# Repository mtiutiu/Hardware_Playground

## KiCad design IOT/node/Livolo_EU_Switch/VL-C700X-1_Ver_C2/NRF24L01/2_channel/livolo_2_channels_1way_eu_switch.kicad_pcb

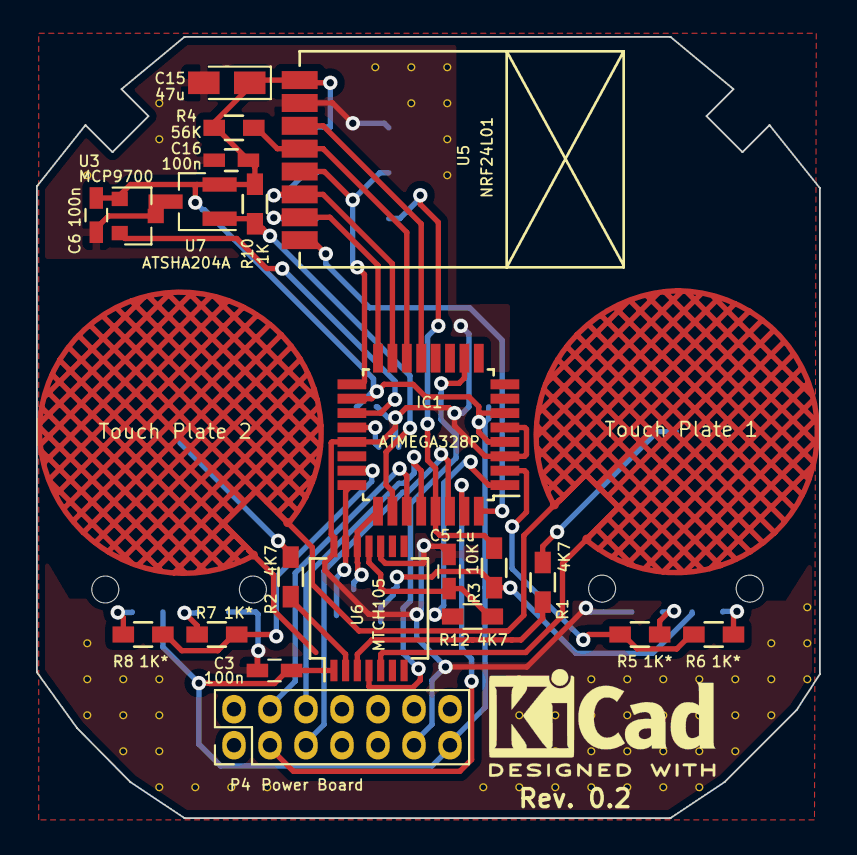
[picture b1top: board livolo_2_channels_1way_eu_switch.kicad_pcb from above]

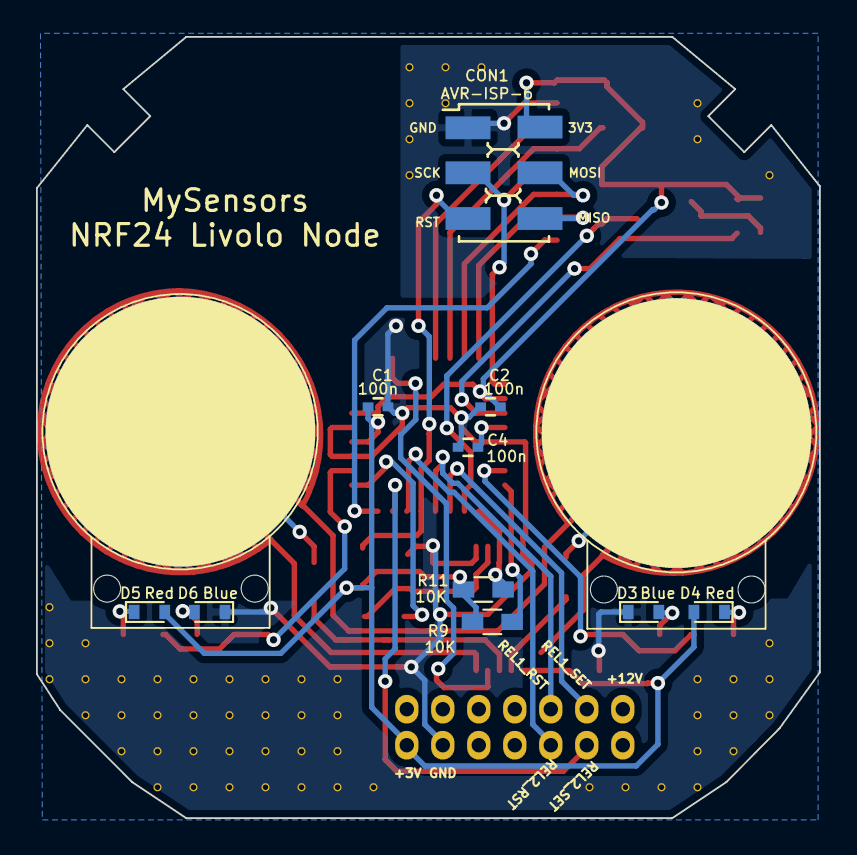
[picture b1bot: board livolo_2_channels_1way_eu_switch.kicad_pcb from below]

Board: 2 copper layers, 43.5 x 43.4 mm, 90 parts (10 on the bottom side), 32 nets.

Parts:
C1, C2, C4: 100n; C_0402
C3, C6, C16: 100n; C_0603_HandSoldering
C5: 1u; C_0603_HandSoldering
C15: 47u; CP_Tantalum_Case-R_EIA-2012-12_Wave
CON1: AVR-ISP-6; AVR_ISP_SMT_Small_02x03
D3, D6: Blue; D_0603
D4, D5: Red; D_0603
IC1: ATMEGA328P; TQFP-32_7x7mm_Pitch0.8mm
P4: Power Board; Pin_Header_Straight_2x07_Pitch2.00mm
R1, R2, R12: 4K7; R_0603_HandSoldering
R3, R9, R11: 10K; R_0603_HandSoldering
R4: 56K; R_0603_HandSoldering
R5, R6, R7, R8: 1K*; R_0603_HandSoldering
R10: 1K; R_0603_HandSoldering
U1: Touch Plate 2; livolo_ts_guard_cut_simple
U2: Touch Plate 1; livolo_ts_guard_cut_simple
U3: MCP9700; SOT-23
U5: NRF24L01; NRF24L01-SMD
U6: MTCH105; SSOP-14_5.3x6.2mm_Pitch0.65mm
U7: ATSHA204A; SOT-23_Handsoldering
V2_4, V2_17, V2_18, V2_19, V3_18, V3_19, V3_20, V4_2, V4_3, V4_18, V4_19, V4_20, V4_21, V5_21, V6_21, V7_21, V10_1, V11_1, V11_2, V12_1, V12_2, V12_3, V12_4, V13_21, V14_18, V14_19, V14_20, V14_21, V15_18, V15_19, V15_20, V15_21, V16_18, V16_19, V16_20, V16_21, V17_18, V17_19, V17_20, V17_21, V18_18, V18_19, V18_20, V18_21, V19_18, V19_19, V19_20, V19_21, V20_18, V20_19, V20_20, V21_17, V21_18, V21_19, V22_16, V22_17, V22_18: AUTO_VIA; VIA_MATRIX

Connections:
+3V3: C1.1, C2.2, C3.1, C6.2, C15.1, C16.2, CON1.2, D4.2, D5.2, IC1.4, IC1.6, IC1.18, P4.13, R3.1, R4.2, R9.1, R10.1, R11.1, U3.1, U5.2, U6.1, U7.2
/ATSHA204A: IC1.26, R10.2, U7.1
/MISO: CON1.6, IC1.16, U5.7
/MOSI: CON1.4, IC1.15, U5.6
/MTPM: IC1.10, U6.4
/MTSA: IC1.1, R12.1
/RADIO_CE: IC1.13, U5.3
/RADIO_CSN: IC1.14, R4.1, U5.4
/RADIO_IRQ: IC1.32, U5.8
/RESET: CON1.5, IC1.29, R3.2
/Relay1_Reset: IC1.28, P4.6
/Relay1_Set: IC1.27, P4.4
/Relay2_Reset: IC1.31, P4.3
/Relay2_Set: IC1.30, P4.5
/S1_LEDs: IC1.2, R5.2, R6.2
/S2_LEDs: IC1.23, R7.2, R8.2
/SCK: CON1.3, IC1.17, U5.5
/TEMP_SENS: IC1.19, U3.2
/TS1: IC1.24, R9.2, U6.13
/TS2: IC1.25, R11.2, U6.12
GND: C1.2, C2.1, C3.2, C4.1, C5.2, C6.1, C15.2, C16.1, CON1.1, D3.1, D6.1, IC1.3, IC1.5, IC1.21, P4.11, U3.3, U5.1, U6.10, U6.14, U7.3, V2_4.1, V2_17.1, V2_18.1, V2_19.1, V3_18.1, V3_19.1, V3_20.1, V4_2.1, V4_3.1, V4_18.1, V4_19.1, V4_20.1, V4_21.1, V5_21.1, V6_21.1, V7_21.1, V10_1.1, V11_1.1, V11_2.1, V12_1.1, V12_2.1, V12_3.1, V12_4.1, V13_21.1, V14_18.1, V14_19.1, V14_20.1, V14_21.1, V15_18.1, V15_19.1, V15_20.1, V15_21.1, V16_18.1, V16_19.1, V16_20.1, V16_21.1, V17_18.1, V17_19.1, V17_20.1, V17_21.1, V18_18.1, V18_19.1, V18_20.1, V18_21.1, V19_18.1, V19_19.1, V19_20.1, V19_21.1, V20_18.1, V20_19.1, V20_20.1, V21_17.1, V21_18.1, V21_19.1, V22_16.1, V22_17.1, V22_18.1
unnamed: C4.2, IC1.20
unnamed: C5.1, R12.2, U6.11
unnamed: D3.2, R7.1
unnamed: D4.1, R8.1
unnamed: D5.1, R6.1
unnamed: D6.2, R5.1
unnamed: R1.1, U6.3
unnamed: R1.2, U2.1
unnamed: R2.1, U1.1
unnamed: R2.2, U6.2
unnamed: U1.2, U2.2, U6.5

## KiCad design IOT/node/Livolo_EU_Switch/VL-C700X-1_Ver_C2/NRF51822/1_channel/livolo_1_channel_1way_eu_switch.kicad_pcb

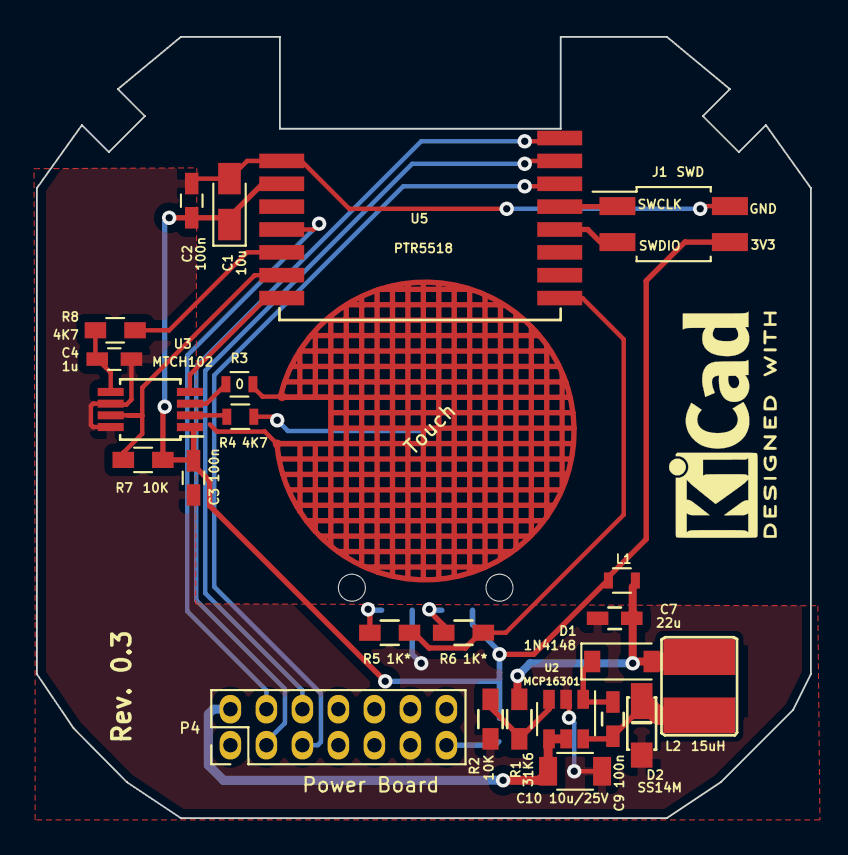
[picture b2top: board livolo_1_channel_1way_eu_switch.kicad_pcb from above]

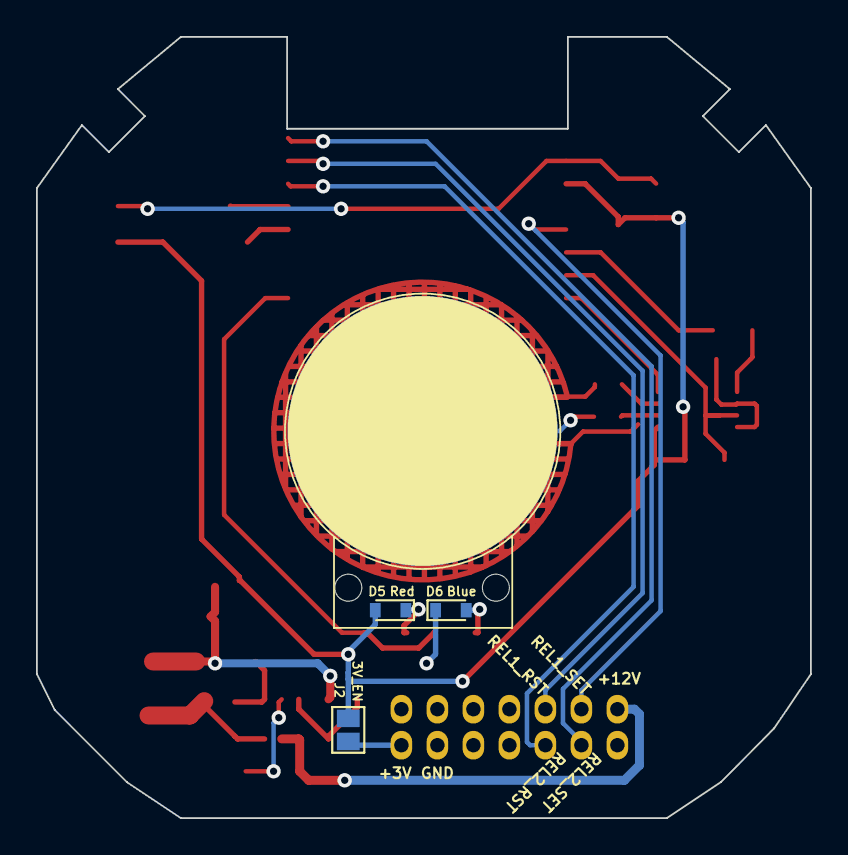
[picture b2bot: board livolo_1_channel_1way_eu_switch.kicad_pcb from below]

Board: 2 copper layers, 43.0 x 43.4 mm, 28 parts (3 on the bottom side), 25 nets.

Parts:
C1: 10u; CP_Tantalum_Case-R_EIA-2012-12_Wave
C2, C3, C9: 100n; C_0603_HandSoldering
C4: 1u; C_0603_HandSoldering
C7: 22u; C_0603_HandSoldering
C10: 10u/25V; C_1206
D1: 1N4148; SOD-123
D2: SS14M
D5: Red; D_0603
D6: Blue; D_0603
J1: SWD; Pin_Header_Straight_2x02_Pitch2.00mm_SMD
J2: 3V_EN; GS2
L1: BLM18HE152SN1D; R_0603
L2: 15uH; VLCF4020T-150MR68
P4: Power Board; Pin_Header_Straight_2x07_Pitch2.00mm
R1: 31K6; R_0603_HandSoldering
R2, R7: 10K; R_0603_HandSoldering
R3: 0; R_0603
R4: 4K7; R_0603
R5, R6: 1K*; R_0603_HandSoldering
R8: 4K7; R_0603_HandSoldering
U1: Touch; livolo_ts_guard
U2: MCP16301; SOT-23-6
U3: MTCH102; MSOP-8_3x3mm_Pitch0.65mm
U5: PTR5518

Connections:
+3V3: C1.1, C2.2, C3.2, D5.2, J1.4, J2.2, L1.2, R7.2, U3.1, U5.10
/12Vcc: C10.1, P4.2, U2.4, U2.5
/MTPM: U3.4, U5.15
/MTSA: R8.1, U5.13
/Relay1_Reset: P4.6, U5.7
/Relay1_Set: P4.4, U5.12
/Relay2_Reset: P4.3, U5.8
/Relay2_Set: P4.5, U5.6
/S1_LEDs: R5.2, R6.2, U5.1
/SWCLK: J1.1, U5.5
/SWDIO: J1.3, U5.4
/TS1: R7.1, U3.7, U5.14
GND: C1.2, C2.1, C3.1, C4.2, C7.2, C10.2, D2.2, D6.1, J1.2, P4.11, R2.1, U2.2, U3.6, U3.8, U5.9
unnamed: C4.1, R8.2, U3.5
unnamed: C7.1, D1.2, L1.1, L2.1, R1.2
unnamed: C9.1, D1.1, U2.1
unnamed: C9.2, D2.1, L2.2, U2.6
unnamed: D5.1, R6.1
unnamed: D6.2, R5.1
unnamed: J2.1, P4.13
unnamed: R1.1, R2.2, U2.3
unnamed: R3.1, U3.3
unnamed: R3.2, U1.2
unnamed: R4.1, U3.2
unnamed: R4.2, U1.1

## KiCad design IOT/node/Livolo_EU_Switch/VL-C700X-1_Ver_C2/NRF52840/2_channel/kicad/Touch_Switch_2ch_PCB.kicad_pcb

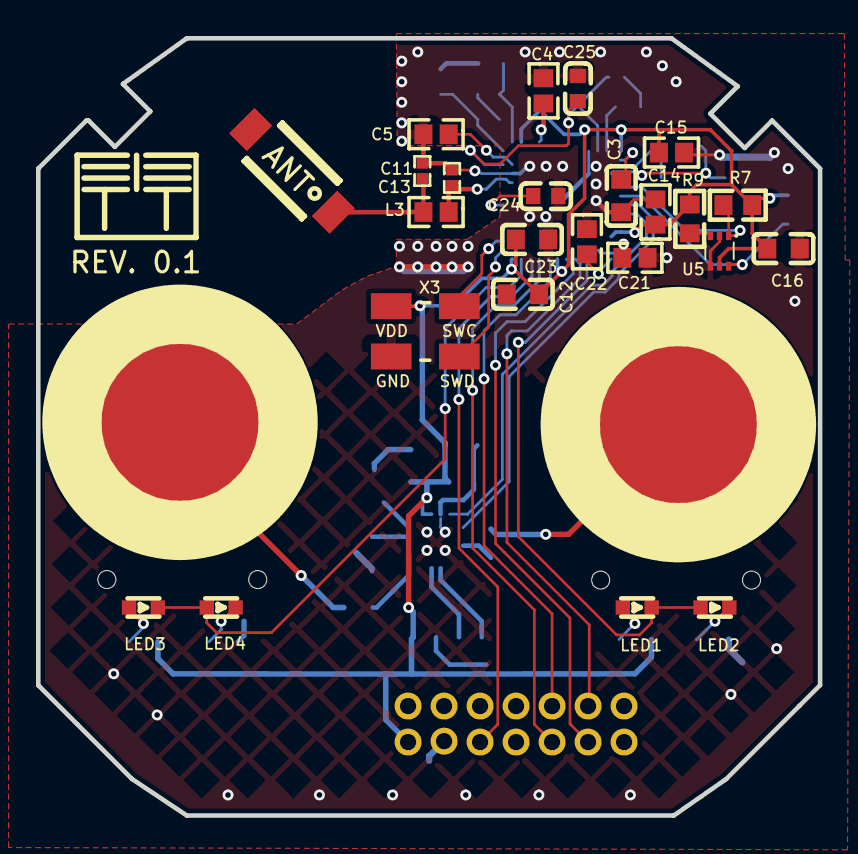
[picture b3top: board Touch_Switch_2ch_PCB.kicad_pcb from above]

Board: 2 copper layers, 43.4 x 43.2 mm, 53 parts (0 on the bottom side), 43 nets.

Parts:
ALG: my_logo; ggeac4e8891367b2b2c
C1, C15, C17: 1uF; 0603
C2, C3, C12, C16, C18, C19, C20, C23: 100nF; C0603
C4: N.C.; 0603
C5: 100pF; 0603
C6: 2.2nF; C0603
C7, C8, C9, C10: 22pF; 0603
C11: 0.8pF; 0402
C13: 0.5pF; 0402
C14, C21, C22: 4.7uF; 0603
C24: 820pF; C0603
C25: 47nF; C0603
CN1: 2X7P; HDR-TH_14P-P2.00-V-R2-C7-S2.00_A2005HWV-2X7P
H1: PROG; CONNECTER_SMD_1.27_1X4_D180
L2: 10uH; 0603
L3: 4.7nH; 0603
L4: 15nH; 0402
LED1, LED3: RED; LED-SMD_0603-T
LED2, LED4: BLUE; LED-SMD_0603-T
R1, R2, R5, R6, R7, R8, R9: 4.7K; R0603
R3, R10: 560; R0603
U1: NRF52840-QIAA-R; AQFN-73_L7.0-W7.0-P0.50-BL-EP4.8
U2, U7: TS1; LIVOLO_TOUCH_PAD
U3: Antenna 2.4GHz; AN6520
U5: TMP112; SOT-563_L1.6-W1.2-P0.50-LS1.6-BL
U6: CY8C4014LQI-421T; QFN-16_L3.0-W3.0-P0.50-BL-EP1.7
X1: 32MHz; OSC-SMD_4P-L2.0-W1.6-BL
X2: 32.768KHz; FC-135R_L3.2-W1.5
X3: ICSP; SWD4_5032

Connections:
ANT: C11.1, L3.1, U1.H23
C4_2: C4.2, U1.A18
CH1_LED: LED1.1, LED2.2, U1.AD8
CH2_LED: LED3.1, LED4.2, U1.AD22
DCC: L2.1, U1.B3
DEC4_6: C1.1, C25.2, L4.2, U1.B5, U1.E24
GND: C1.2, C2.1, C3.2, C4.1, C5.2, C6.2, C7.2, C8.2, C9.1, C10.1, C11.2, C12.1, C13.2, C14.2, C15.1, C16.2, C17.1, C18.1, C19.1, C20.1, C21.1, C22.1, C23.1, C24.1, C25.1, CN1.11, H1.3, R2.2, R5.2, U1.0, U1.B7, U1.F23, U5.2, U5.4, U6.7, X1.2, X1.4, X3.3
L2_2: L2.2, L4.1
L3_2: C13.1, L3.2, U3.1
LED2_1: LED2.1, R5.1
LED3_2: LED3.2, R1.1
MTO1: U1.R1, U6.8
MTO2: U1.N1, U6.9
R1_RST: CN1.6, U1.AD16
R1_SET: CN1.4, U1.AD10
R2_1: LED4.1, R2.1
R2_RST: CN1.3, U1.AD12
R2_SET: CN1.5, U1.AD18
R3_1: R3.1, U2.1
R6_1: LED1.2, R6.1
R9_1: R9.1, U5.3
R10_1: R10.1, U7.1
SCL: R7.2, U1.J1, U5.1
SDA: R8.2, U1.L1, U5.6
SWC: H1.2, U6.15
SWCLK: U1.AA24, X3.1
SWD: H1.1, U6.14
SWDIO: U1.AC24, X3.4
U1_AC5: C21.2, U1.AC5
U1_AD2: C22.2, U1.AD2
U1_C1: C3.1, U1.C1
U1_D23: C5.1, U1.D23
U1_N24: C24.2, U1.N24
U6_1: R3.2, U6.1
U6_3: C6.1, U6.3
U6_4: C19.2, U6.4
U6_11: R10.2, U6.11
VDD: C2.2, C12.2, C14.1, C15.2, C16.1, C17.2, C18.2, C20.2, C23.2, CN1.13, H1.4, R1.2, R6.2, R7.1, R8.1, R9.2, U1.A22, U1.AD14, U1.AD23, U1.B1, U1.W1, U1.Y2, U5.5, U6.5, U6.6, X3.2
VSENSE: CN1.9, U1.AD20
XC1: C7.1, U1.B24, X1.1
XC2: C8.1, U1.A23, X1.3
XL1: C9.2, U1.D2, X2.1
XL2: C10.2, U1.F2, X2.2

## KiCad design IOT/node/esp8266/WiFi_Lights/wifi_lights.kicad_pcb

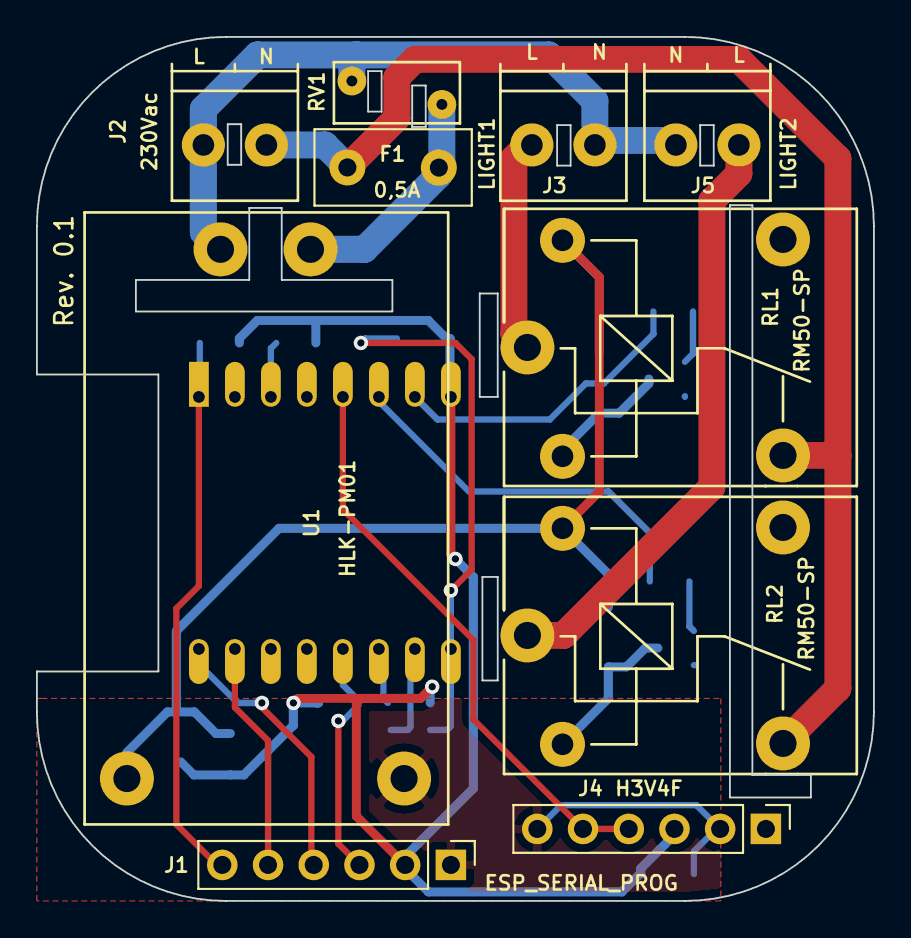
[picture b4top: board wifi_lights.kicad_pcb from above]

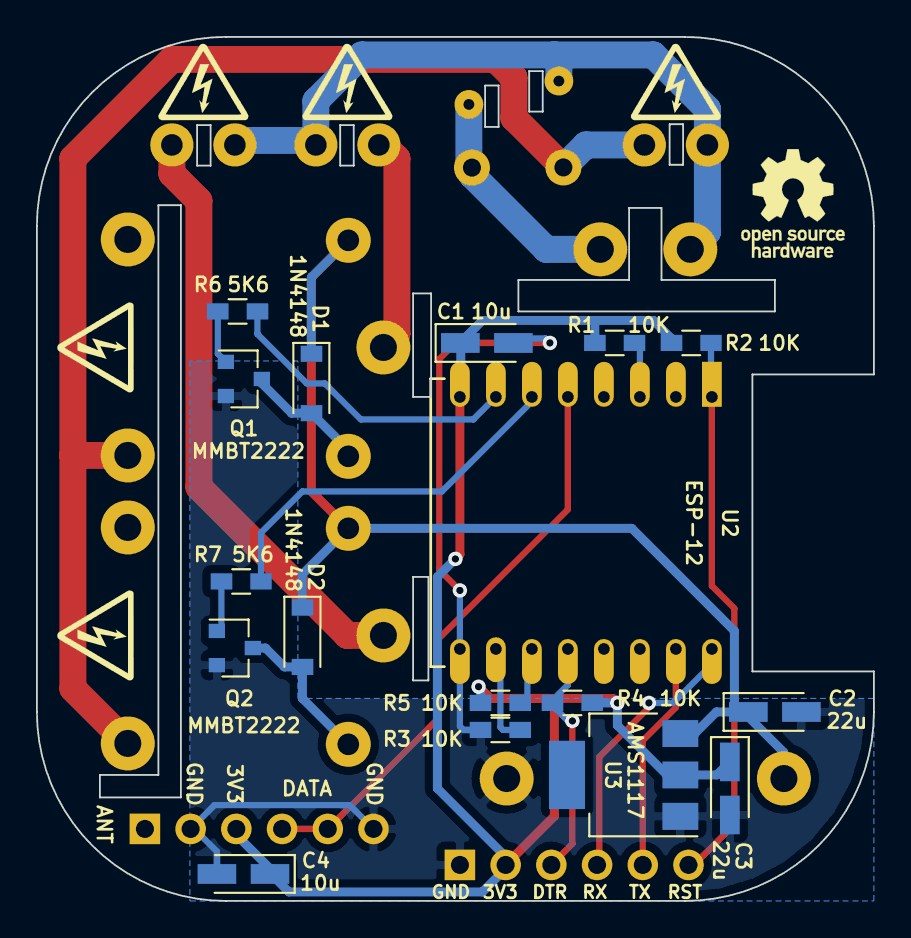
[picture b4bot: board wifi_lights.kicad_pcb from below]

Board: 2 copper layers, 46.5 x 48.0 mm, 27 parts (17 on the bottom side), 22 nets.

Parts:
C1, C4: 10u; CP_Tantalum_Case-A_EIA-3216-18_Wave
C2, C3: 22u; CP_Tantalum_Case-A_EIA-3216-18_Wave
D1, D2: 1N4148; D_SOD-123
F1: 0,5A; Fuse_TE5_Littlefuse-395Series
J1: ESP_SERIAL_PROG; Pin_Header_Straight_1x06_Pitch2.54mm
J2: 230Vac; TerminalBlock_Pheonix_PT-3.5mm_2pol
J3: LIGHT1; TerminalBlock_Pheonix_PT-3.5mm_2pol
J4: H3V4F; Pin_Header_Straight_1x06_Pitch2.54mm
J5: LIGHT2; TerminalBlock_Pheonix_PT-3.5mm_2pol
Q1, Q2: MMBT2222; SOT-23
R1, R2, R3, R4, R5: 10K; R_0603_HandSoldering
R6, R7: 5K6; R_0603_HandSoldering
RL1, RL2: RM50-SP; RM50_P
RV1: Varistor; RV_Disc_D7_W3.4_P5
U1: ESP-12
U2: HLK-PM01
U3: AMS1117; SOT-223

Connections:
+3V3: C1.1, C3.1, C4.1, J1.2, J4.3, R1.2, R2.2, R4.2, R5.2, U1.8, U3.2
+5V: C2.1, D1.1, D2.1, RL1.A1, RL2.A1, U2.3, U3.3
/433_RX_DATA: J4.4, J4.5, U1.5
/DTR: J1.3, R4.1, U1.12
/L: F1.1, J2.1, RL1.14, RL2.14
/N: J2.2, J3.1, J5.2, RV1.2, U2.2
/RELAY_CH1: R6.2, U1.7
/RELAY_CH2: R7.2, U1.6
/REL_SW1: J3.2, RL1.11
/REL_SW2: J5.1, RL2.11
/RESET: J1.6, R2.1, U1.1
/RX: J1.4, U1.16
/TX: J1.5, U1.15
GND: C1.2, C2.2, C3.2, C4.2, J1.1, J4.2, J4.6, Q1.2, Q2.2, R3.1, U1.9, U2.4, U3.1
unnamed: D1.2, Q1.3, RL1.A2
unnamed: D2.2, Q2.3, RL2.A2
unnamed: F1.2, RV1.1, U2.1
unnamed: Q1.1, R6.1
unnamed: Q2.1, R7.1
unnamed: R1.1, U1.3
unnamed: R3.2, U1.10
unnamed: R5.1, U1.11

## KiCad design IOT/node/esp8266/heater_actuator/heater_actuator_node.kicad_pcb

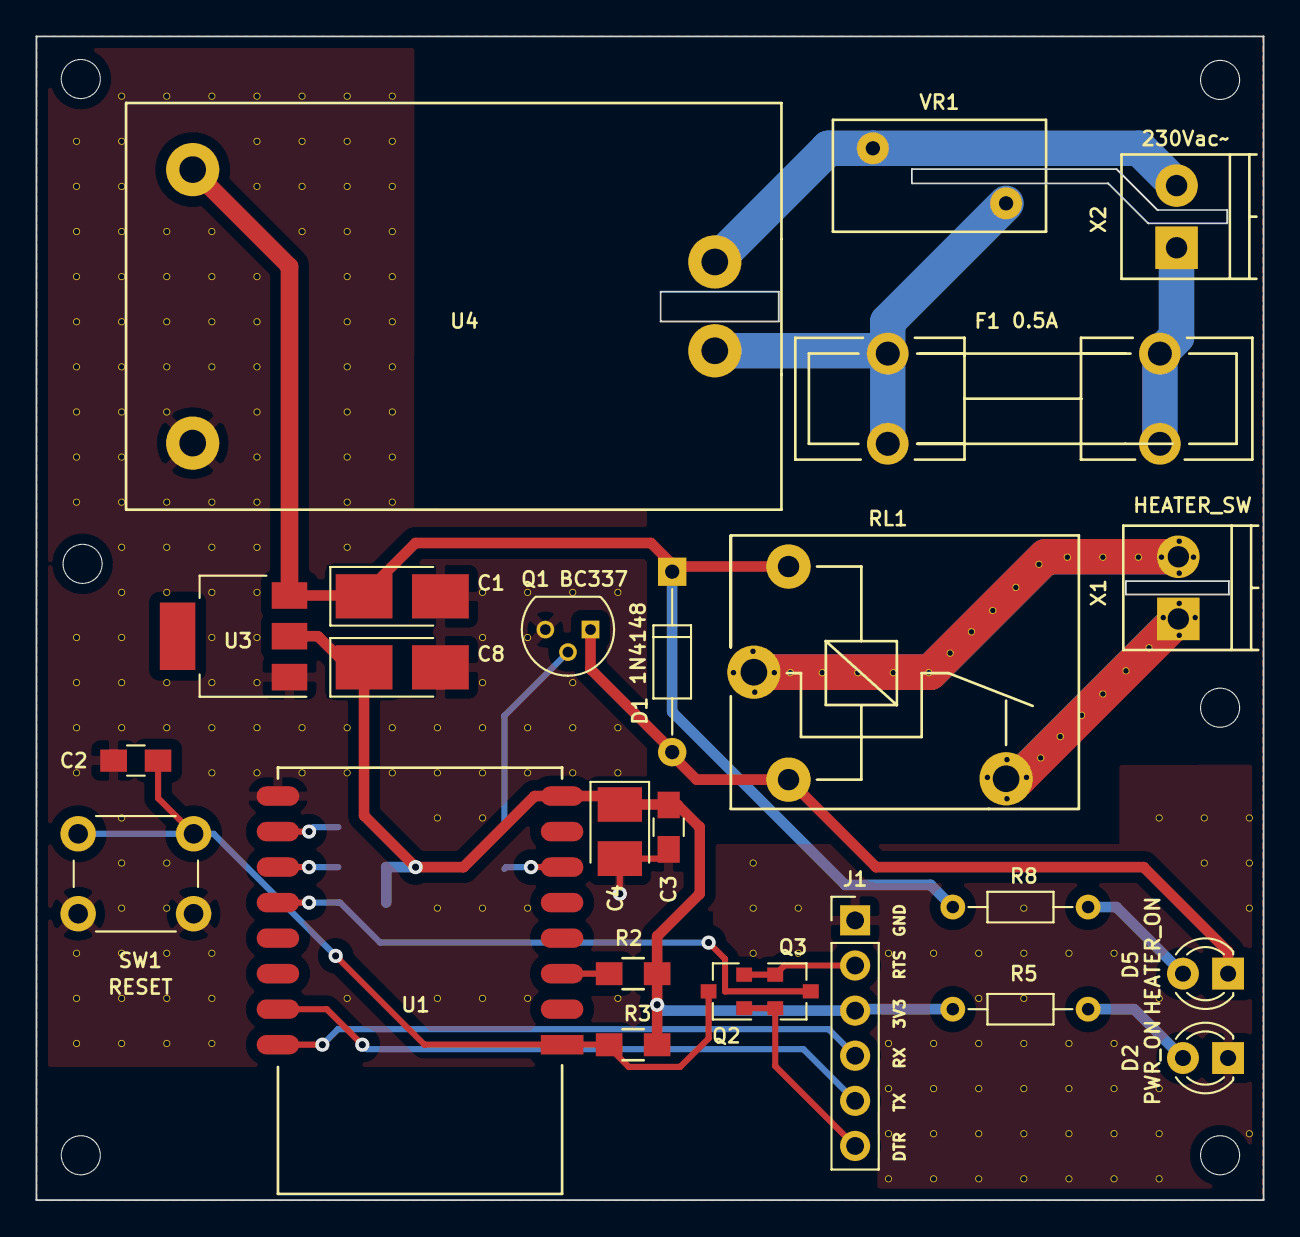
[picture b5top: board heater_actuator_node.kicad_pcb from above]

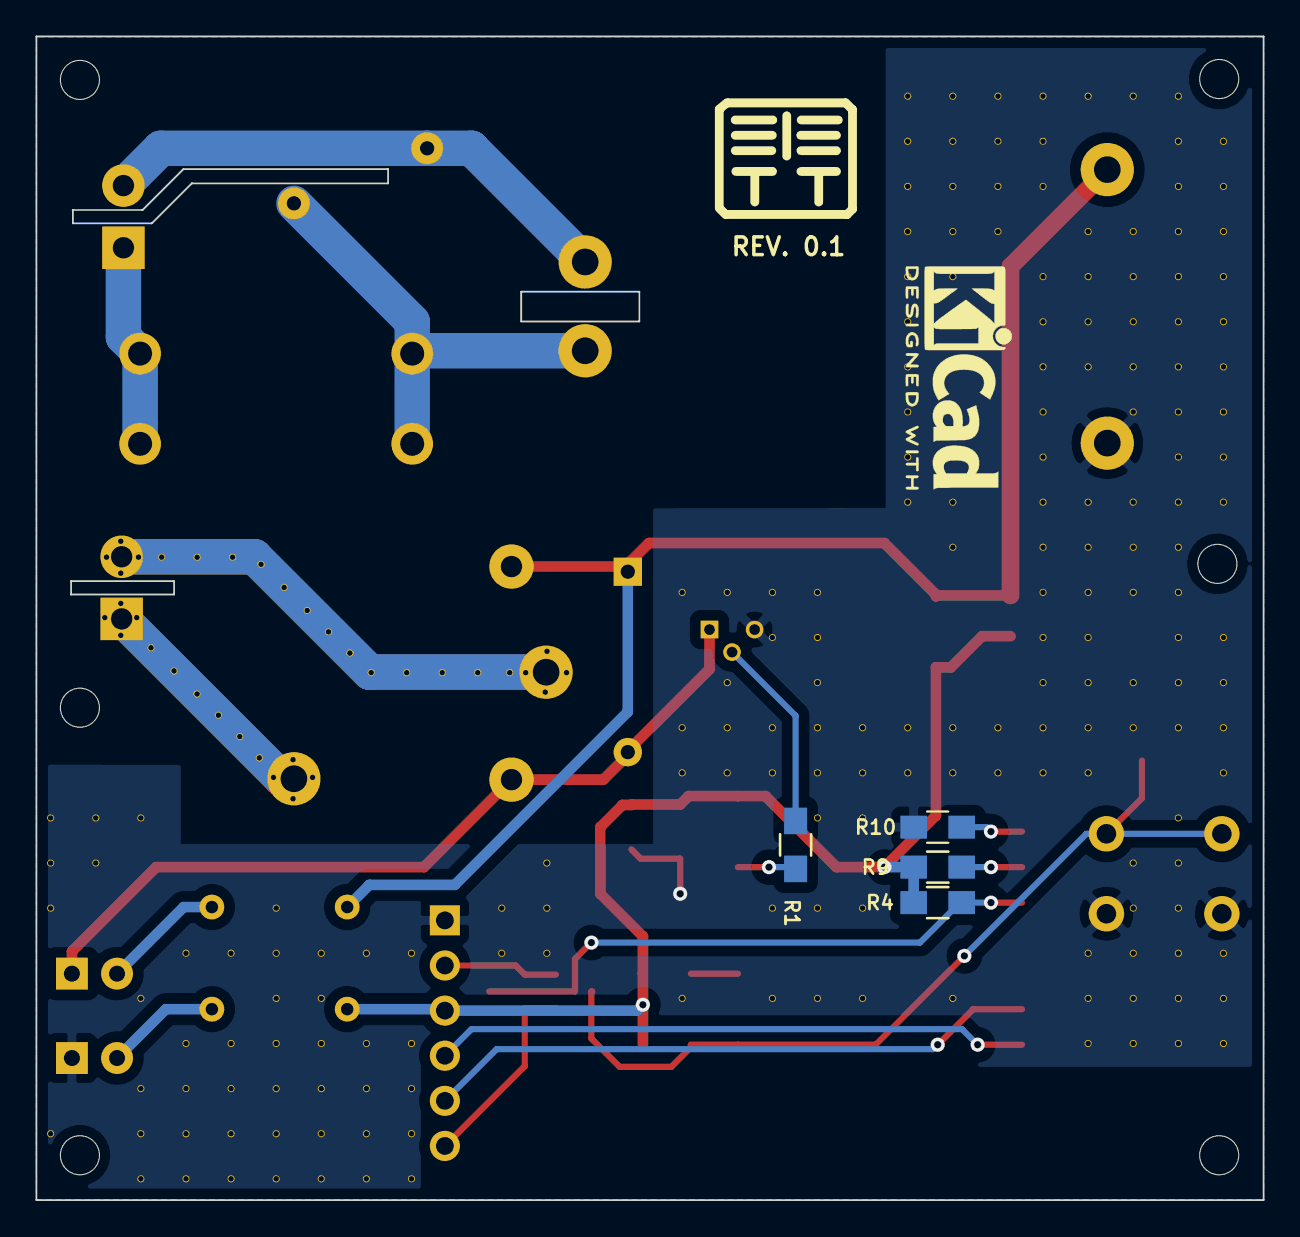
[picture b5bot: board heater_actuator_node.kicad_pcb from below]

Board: 2 copper layers, 69.1 x 65.5 mm, 255 parts (4 on the bottom side), 22 nets.

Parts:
C1, C8: 22u; CP_Tantalum_Case-B_EIA-3528-21_Hand
C2, C3: 100n; C_0805_HandSoldering
C4: 22u; CP_Tantalum_Case-B_EIA-3528-21_Reflow
D1: 1N4148; D_DO-35_SOD27_P10.16mm_Horizontal
D2: PWR_ON; LED_D3.0mm
D5: HEATER_ON; LED_D3.0mm
F1: 0.5A; Fuseholder5x20_horiz_open_lateral_Type-II
J1: Conn_01x06; Pin_Header_Straight_1x06_Pitch2.54mm
Q1: BC337; TO-92_Molded_Narrow
Q2, Q3: MMBT3904; SOT-23
R1: 5K6; R_0805_HandSoldering
R2, R3, R4, R9, R10: 10K; R_0805_HandSoldering
R5, R8: 330; R_Axial_DIN0204_L3.6mm_D1.6mm_P7.62mm_Horizontal
RL1: RM50-SP; RM50_SP
SW1: RESET; SW_PUSH_6mm
U1: ESP-12
U3: AMS1117-3.3; SOT-223
U4: HLK-PM01
V3_3, V3_4, V3_5, V3_6, V3_7, V3_8, V3_9, V3_10, V3_11, V3_14, V3_15, V3_16, V3_17, V3_21, V3_22, V3_23, V4_2, V4_3, V4_4, V4_5, V4_6, V4_7, V4_8, V4_9, V4_10, V4_11, V4_12, V4_13, V4_14, V4_15, V4_16, V4_18, V4_19, V4_20, V4_21, V4_22, V4_23, V5_2, V5_5, V5_6, V5_7, V5_8, V5_9, V5_11, V5_12, V5_13, V5_15, V5_16, V5_19, V5_20, V5_21, V5_22, V5_23, V6_2, V6_5, V6_6, V6_7, V6_8, V6_11, V6_12, V6_13, V6_14, V6_15, V6_16, V6_17, V6_21, V6_22, V6_23, V7_2, V7_3, V7_4, V7_6, V7_7, V7_8, V7_9, V7_10, V7_11, V7_12, V7_13, V7_14, V7_15, V7_16, V7_17, V8_2, V8_3, V8_4, V8_5, V8_16, V8_17, V9_2, V9_3, V9_4, V9_5, V9_6, V9_7, V9_8, V9_9, V9_10, V9_11, V9_12, V9_16, V9_17, V9_22, V10_2, V10_3, V10_4, V10_5, V10_6, V10_7, V10_8, V10_9, V10_10, V10_11, V10_16, V10_17, V11_16, V11_17, V11_18, V11_20, V11_22, V12_13, V12_14, V12_15, V12_16, V12_17, V12_18, V12_20, V12_22, V13_13, V13_14, V13_16, V13_17, V13_20, V13_22, V14_13, V14_15, V14_16, V14_17, V15_13, V15_16, V15_17, V15_22, V18_19, V18_20, V18_21, V19_20, V19_21, V21_21, V21_23, V21_24, V21_25, V21_26, V22_21, V22_23, V22_24, V22_25, V22_26, V23_21, V23_22, V23_23, V23_24, V23_25, V23_26, V24_20, V24_21, V24_22, V24_23, V24_24, V24_25, V24_26, V25_21, V25_23, V25_24, V25_25, V25_26, V26_21, V26_23, V26_24, V26_25, V26_26, V27_18, V27_18#2, V27_18#3, V27_18#4, V27_18#5, V27_18#6, V27_18#7, V27_18#8, V27_18#9, V27_18#10, V27_18#11, V27_18#12, V27_18#13, V27_18#14, V27_18#15, V27_18#16, V27_18#17, V27_18#18, V27_18#19, V27_18#20, V27_18#21, V27_18#22, V27_18#23, V27_18#24, V27_18#25, V27_18#26, V27_18#27, V27_18#28, V27_18#29, V27_18#30, V27_18#31, V27_18#32, V27_18#33, V27_18#34, V27_18#35, V27_18#36, V27_22, V27_24, V27_25, V27_26, V28_18, V28_19, V29_18, V29_19, V29_20, V29_25: AUTO_VIA; VIA_MATRIX
VR1: VAR10-300; RV_Disc_D12_W6.3_P7.5
X1: HEATER_SW; TerminalBlock_Pheonix_PT-3.5mm_2pol
X2: 230Vac~~; TerminalBlock_Pheonix_PT-3.5mm_2pol

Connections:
+3V3: C3.1, C4.1, C8.1, J1.3, R2.2, R3.2, R4.2, R5.1, R9.2, U1.8, U3.2
+5V: C1.1, D1.1, R8.1, RL1.A1, U3.3, U4.3
/DTR: J1.6, Q2.1, Q3.2
/EN: R2.1, U1.3
/GPIO0: Q3.3, R4.1, U1.12
/GPIO2: R9.1, U1.11
/GPIO15: R10.1, U1.10
/H_RELAY_CMD: R1.2, U1.6
/RESET: C2.1, Q2.3, R3.1, SW1.1, U1.1
/RTS: J1.2, Q2.2, Q3.1
/RX: J1.4, U1.16
/TX: J1.5, U1.15
GND: C1.2, C2.2, C3.2, C4.2, C8.2, D2.1, J1.1, Q1.3, R10.2, SW1.2, U1.9, U3.1, U4.4, V3_3.1, V3_4.1, V3_5.1, V3_6.1, V3_7.1, V3_8.1, V3_9.1, V3_10.1, V3_11.1, V3_14.1, V3_15.1, V3_16.1, V3_17.1, V3_21.1, V3_22.1, V3_23.1, V4_2.1, V4_3.1, V4_4.1, V4_5.1, V4_6.1, V4_7.1, V4_8.1, V4_9.1, V4_10.1, V4_11.1, V4_12.1, V4_13.1, V4_14.1, V4_15.1, V4_16.1, V4_18.1, V4_19.1, V4_20.1, V4_21.1, V4_22.1, V4_23.1, V5_2.1, V5_5.1, V5_6.1, V5_7.1, V5_8.1, V5_9.1, V5_11.1, V5_12.1, V5_13.1, V5_15.1, V5_16.1, V5_19.1, V5_20.1, V5_21.1, V5_22.1, V5_23.1, V6_2.1, V6_5.1, V6_6.1, V6_7.1, V6_8.1, V6_11.1, V6_12.1, V6_13.1, V6_14.1, V6_15.1, V6_16.1, V6_17.1, V6_21.1, V6_22.1, V6_23.1, V7_2.1, V7_3.1, V7_4.1, V7_6.1, V7_7.1, V7_8.1, V7_9.1, V7_10.1, V7_11.1, V7_12.1, V7_13.1, V7_14.1, V7_15.1, V7_16.1, V7_17.1, V8_2.1, V8_3.1, V8_4.1, V8_5.1, V8_16.1, V8_17.1, V9_2.1, V9_3.1, V9_4.1, V9_5.1, V9_6.1, V9_7.1, V9_8.1, V9_9.1, V9_10.1, V9_11.1, V9_12.1, V9_16.1, V9_17.1, V9_22.1, V10_2.1, V10_3.1, V10_4.1, V10_5.1, V10_6.1, V10_7.1, V10_8.1, V10_9.1, V10_10.1, V10_11.1, V10_16.1, V10_17.1, V11_16.1, V11_17.1, V11_18.1, V11_20.1, V11_22.1, V12_13.1, V12_14.1, V12_15.1, V12_16.1, V12_17.1, V12_18.1, V12_20.1, V12_22.1, V13_13.1, V13_14.1, V13_16.1, V13_17.1, V13_20.1, V13_22.1, V14_13.1, V14_15.1, V14_16.1, V14_17.1, V15_13.1, V15_16.1, V15_17.1, V15_22.1, V18_19.1, V18_20.1, V18_21.1, V19_20.1, V19_21.1, V21_21.1, V21_23.1, V21_24.1, V21_25.1, V21_26.1, V22_21.1, V22_23.1, V22_24.1, V22_25.1, V22_26.1, V23_21.1, V23_22.1, V23_23.1, V23_24.1, V23_25.1, V23_26.1, V24_20.1, V24_21.1, V24_22.1, V24_23.1, V24_24.1, V24_25.1, V24_26.1, V25_21.1, V25_23.1, V25_24.1, V25_25.1, V25_26.1, V26_21.1, V26_23.1, V26_24.1, V26_25.1, V26_26.1, V27_18#36.1, V27_22.1, V27_24.1, V27_25.1, V27_26.1, V28_18.1, V28_19.1, V29_18.1, V29_19.1, V29_20.1, V29_25.1
unnamed: D1.2, D5.1, Q1.1, RL1.A2
unnamed: D2.2, R5.2
unnamed: D5.2, R8.2
unnamed: F1.1, U4.1, VR1.1
unnamed: F1.2, X2.1
unnamed: Q1.2, R1.1
unnamed: RL1.11, V27_18.1, V27_18#2.1, V27_18#3.1, V27_18#18.1, V27_18#19.1, V27_18#20.1, V27_18#21.1, V27_18#22.1, V27_18#23.1, V27_18#24.1, V27_18#25.1, V27_18#26.1, V27_18#27.1, V27_18#28.1, V27_18#29.1, V27_18#30.1, V27_18#31.1, V27_18#32.1, V27_18#33.1, V27_18#34.1, V27_18#35.1, X1.2
unnamed: RL1.14, V27_18#4.1, V27_18#5.1, V27_18#6.1, V27_18#7.1, V27_18#8.1, V27_18#9.1, V27_18#10.1, V27_18#11.1, V27_18#12.1, V27_18#13.1, V27_18#14.1, V27_18#15.1, V27_18#16.1, V27_18#17.1, X1.1
unnamed: U4.2, VR1.2, X2.2

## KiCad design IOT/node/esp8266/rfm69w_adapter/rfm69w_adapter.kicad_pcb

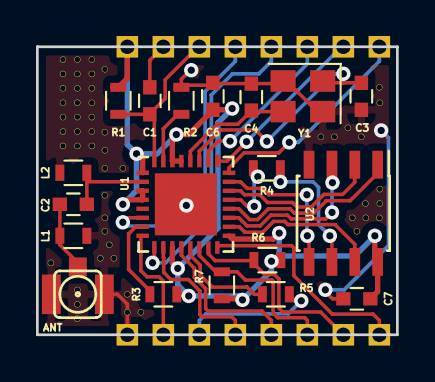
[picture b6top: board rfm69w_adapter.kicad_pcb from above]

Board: 2 copper layers, 20.0 x 16.0 mm, 87 parts (0 on the bottom side), 29 nets.

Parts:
ANT: Antenna_Shield; coaxial_u.fl-r-smt-1
C1: 1u; C_0603
C2: 5p6; C_0603
C3, C4: 10p; C_0603
C6: 10u; C_0603
C7: 100n; C_0603
J1, J2, J3, J4, J5, J6, J7, J8, J9, J10, J11, J12, J13, J14, J15, J16: Conn_01x01; Pin_Header_Straight_1x01_Pitch2.00mm
L1, L2: DNP; L_0603
R1, R3, R5, R6, R7: 10K; R_0603
R2: 12K; R_0603
R4: 200; R_0603
U1: ESP8266EX; QFN-32-1EP_5x5mm_Pitch0.5mm
U2: AT25SF321-SSHDB; SOIC-8_3.9x4.9mm_Pitch1.27mm
V2_4, V2_5, V2_6, V2_7, V2_8, V2_9, V2_10, V3_4, V3_5, V3_6, V3_7, V3_8, V3_9, V3_10, V3_20, V3_21, V3_22, V4_4, V4_5, V4_5#2, V4_6, V4_7, V4_8, V4_9, V4_9#2, V4_10, V5_11, V5_11#2, V5_11#3, V7_21, V7_21#2, V7_21#3, V7_21#4, V7_21#5, V7_21#6, V7_21#7, V7_21#8, V7_21#9, V7_21#10, V22_9, V22_9#2, V22_9#3, V22_9#4, V22_9#5, V23_14, V23_14#2, V23_14#3, V23_14#4, V23_14#5, V24_7, V24_13, V24_14: AUTO_VIA; VIA_MATRIX
Y1: 26MHz; Crystal_SMD_3225-4pin_3.2x2.5mm

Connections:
+3V3: C6.2, C7.2, J9.1, R1.1, R3.1, R6.1, R7.1, U1.1, U1.3, U1.4, U1.11, U1.17, U1.29, U1.30, U2.8
/ADC: J15.1, U1.6
/DTR: C1.1, J13.1
/GPIO0: J8.1, R6.2, U1.15
/GPIO2: J1.1, R7.2, U1.14
/GPIO4: J2.1, U1.16
/GPIO5: J3.1, U1.24
/GPIO12: J4.1, U1.10
/GPIO13: J5.1, U1.12
/GPIO14: J6.1, U1.9
/GPIO16: J7.1, U1.8
/LNA: C2.2, L2.1, U1.2
/RESET: C1.2, J10.1, R1.2, U1.32
/SD_CLK: R4.1, U2.6
/SD_CS: U1.20, U2.1
/SD_HD: U1.18, U2.7
/SD_SI: U1.23, U2.5
/SD_SO: U1.22, U2.2
/SD_WP: U1.19, U2.3
/U0RX: J11.1, U1.26
/U0TX: J14.1, U1.25
GND: ANT.2, C3.2, C4.2, C6.1, C7.1, J12.1, J16.1, L1.2, L2.2, R2.1, R5.2, U1.33, U2.4, V2_4.1, V2_5.1, V2_6.1, V2_7.1, V2_8.1, V2_9.1, V2_10.1, V3_4.1, V3_5.1, V3_6.1, V3_7.1, V3_8.1, V3_9.1, V3_10.1, V3_20.1, V3_21.1, V3_22.1, V4_4.1, V4_5.1, V4_5#2.1, V4_6.1, V4_7.1, V4_8.1, V4_9.1, V4_9#2.1, V4_10.1, V5_11.1, V5_11#2.1, V5_11#3.1, V7_21.1, V7_21#2.1, V7_21#3.1, V7_21#4.1, V7_21#5.1, V7_21#6.1, V7_21#7.1, V7_21#8.1, V7_21#9.1, V7_21#10.1, V22_9.1, V22_9#2.1, V22_9#3.1, V22_9#4.1, V22_9#5.1, V23_14.1, V23_14#2.1, V23_14#3.1, V23_14#4.1, V23_14#5.1, V24_7.1, V24_13.1, V24_14.1, Y1.2, Y1.4
unnamed: ANT.1, C2.1, L1.1
unnamed: C3.1, U1.27, Y1.1
unnamed: C4.1, U1.28, Y1.3
unnamed: R2.2, U1.31
unnamed: R3.2, U1.7
unnamed: R4.2, U1.21
unnamed: R5.1, U1.13

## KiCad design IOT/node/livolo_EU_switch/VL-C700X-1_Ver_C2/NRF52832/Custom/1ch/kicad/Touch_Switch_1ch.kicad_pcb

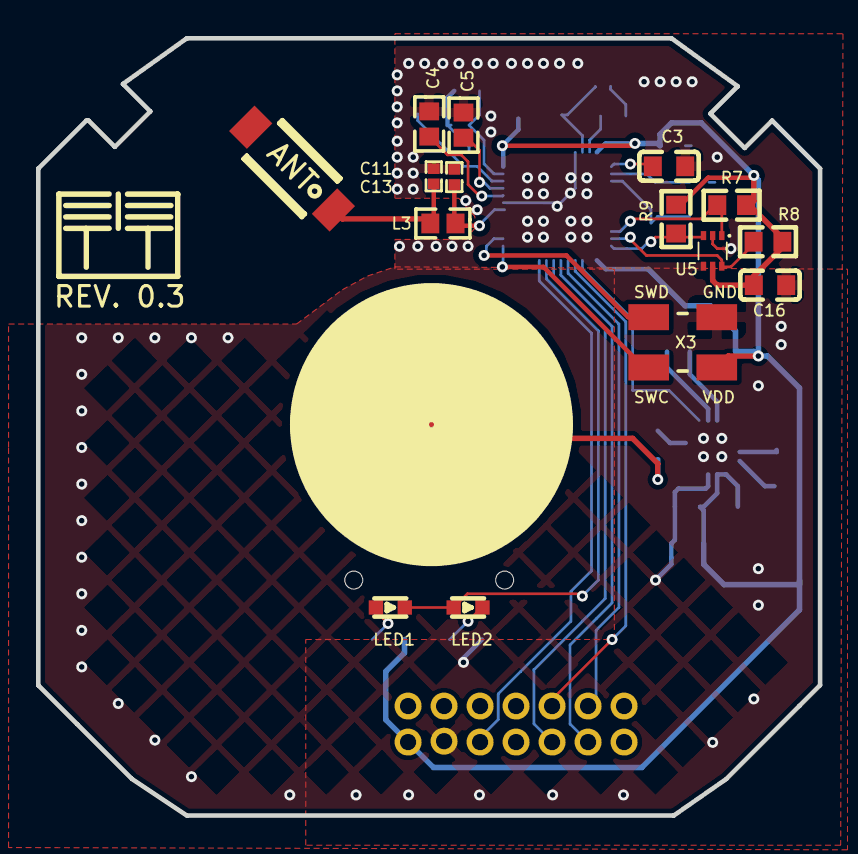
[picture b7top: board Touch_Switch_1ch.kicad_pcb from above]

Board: 2 copper layers, 43.4 x 43.2 mm, 41 parts (0 on the bottom side), 24 nets.

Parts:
C1, C17: 1uF; 0603
C2, C3, C12, C16, C18, C19, C20: 100nF; C0603
C4, C5: 100pF; 0603
C6: 2.2nF; C0603
C7, C8, C9, C10: 22pF; 0603
C11, C13: 0.5pF; 0402
C14: 4.7uF; 0603
CN1: 2X7P; HDR-TH_14P-P2.00-V-R2-C7-S2.00_A2005HWV-2X7P
H1: PROG; CONNECTER_SMD_1.27_1X4_D180
L2: 10uH; 0603
L3: 3.3nH; 0603
L4: 15nH; 0402
LED1: RED; LED-SMD_0603-T
LED2: BLUE; LED-SMD_0603-T
LG: my_logo; gge4275
R5, R6, R7, R8, R9: 4.7K; R0603
R10: 560; R0603
U1: NRF52832; QFN-48_L6.0-W6.0-P0.40-BL-EP3.8
U3: Antenna 2.4GHz; AN6520
U5: TMP112; SOT-563_L1.6-W1.2-P0.50-LS1.6-BL
U6: CY8C4014LQI-421T; QFN-16_L3.0-W3.0-P0.50-BL-EP1.7
U7: TS1; LIVOLO_TOUCH_PAD
X1: 32MHz; OSC-SMD_4P-L2.0-W1.6-BL
X2: 32.768KHz; FC-135R_L3.2-W1.5
X3: ICSP; SWD4_5032

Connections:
CH1_LED: LED1.1, LED2.2, U1.20
GND: C1.2, C2.1, C3.1, C4.1, C5.1, C6.2, C7.2, C8.2, C9.1, C10.1, C11.2, C12.2, C13.2, C14.2, C16.2, C17.1, C18.1, C19.1, C20.1, CN1.11, H1.3, R5.2, U1.31, U1.45, U1.49, U5.2, U5.4, U6.7, U6.17, X1.2, X1.4, X3.3
L2_2: L2.2, L4.1
L3_2: C13.1, L3.2, U3.1
LED2_1: LED2.1, R5.1
MTO: U1.15, U6.13
R1_RST: CN1.6, U1.16
R1_SET: CN1.4, U1.17
R2_RST: CN1.3, U1.18
R2_SET: CN1.5, U1.19
R6_1: LED1.2, R6.1
SWCLK: U1.25, X3.1
SWDIO: U1.26, X3.4
U1_1: C3.2, U1.1
U1_30: C11.1, L3.1, U1.30
U1_32: C4.2, U1.32
U1_33: C5.2, U1.33
U1_46: C1.1, L4.2, U1.46
U1_47: L2.1, U1.47
VDD: C2.2, C12.1, C14.1, C16.1, C17.2, C18.2, C20.2, CN1.13, H1.4, R6.2, R7.1, R8.1, R9.2, U1.13, U1.36, U1.48, U5.5, U6.5, U6.6, X3.2
XC1: C7.1, U1.34, X1.1
XC2: C8.1, U1.35, X1.3
XL1: C9.2, U1.2, X2.1
XL2: C10.2, U1.3, X2.2
